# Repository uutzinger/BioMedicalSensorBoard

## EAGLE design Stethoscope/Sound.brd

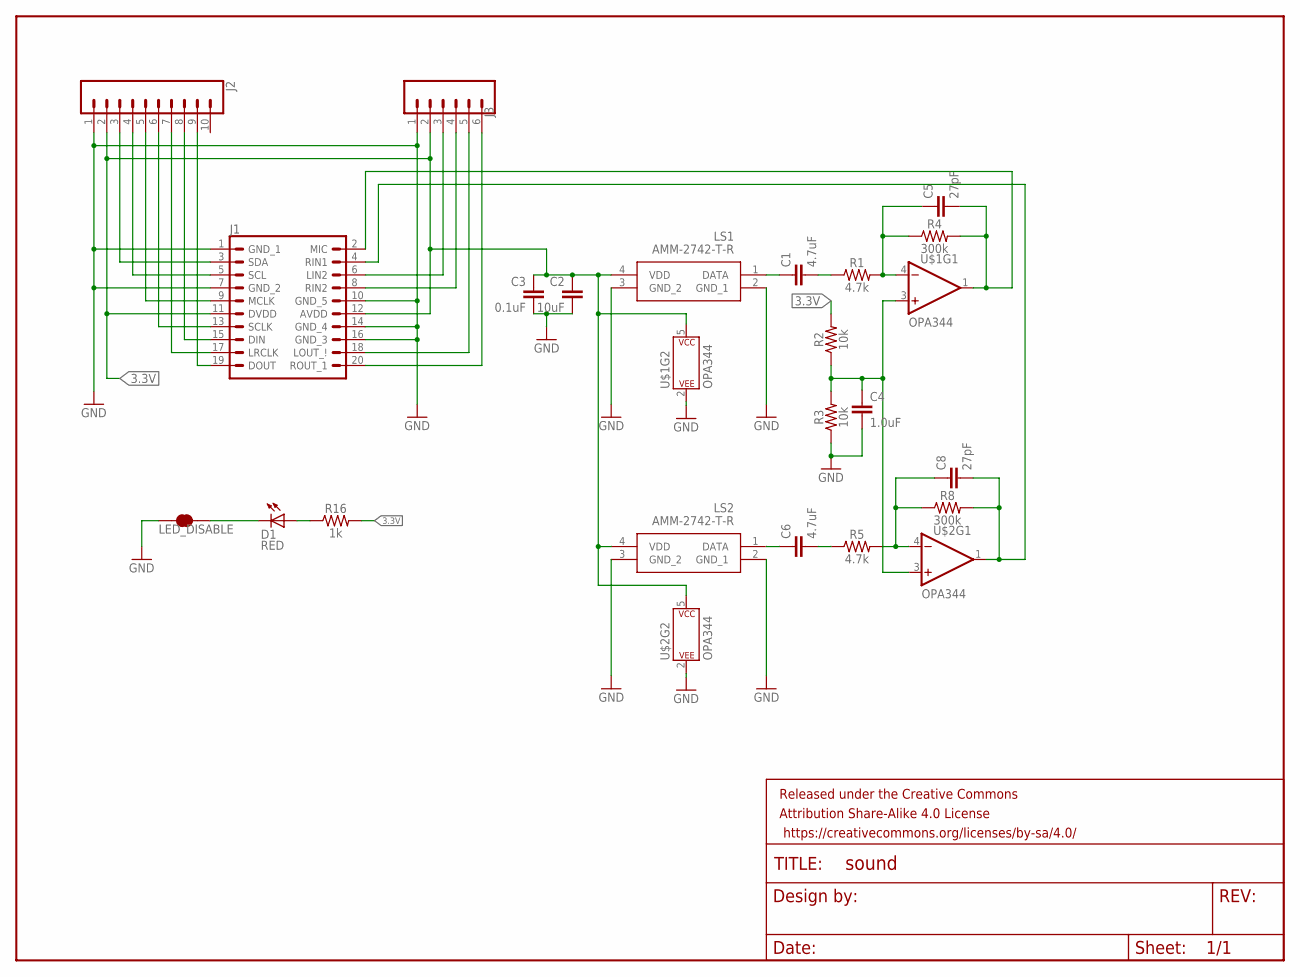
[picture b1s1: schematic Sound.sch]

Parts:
C1, C6: 4.7uF; 0603
C2: 10uF; 0603
C3: 0.1uF; 0603
C4: 1.0uF; 0603
C5, C8: 27pF; 0603
D1: RED; LED-0603
FRAME1: FRAME-LETTERNO_PACKAGE; DUMMY
J1: ES8388ES8388; ES8388
J2: CONN_10"; 1X10
J3: CONN_06SILK_FEMALE_PTH; 1X06
LED_DISABLE: JUMPER-SMT_2_NC_TRACE_SILK; SMT-JUMPER_2_NC_TRACE_SILK
LS1, LS2: AMM-2742-T-R; AMM2742TR
R1, R5: 4.7k; 0603
R2, R3: 10k; 0603
R4, R8: 300k; 0603
R16: 1k; 0603
U$1, U$2: OPA344; SOT23-5

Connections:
3.3V: C2.1, C3.1, J1.11 (DVDD), J1.12 (AVDD), J2.2, J3.2, LS1.4 (VDD), LS2.4 (VDD), R2.2, R16.2, U$1.5 (P$V+), U$2.5 (P$V+)
GND: C2.2, C3.2, C4.2, J1.1 (GND_1), J1.7 (GND_2), J1.10 (GND_5), J1.14 (GND_4), J1.16 (GND_3), J2.1, J3.1, LED_DISABLE.1, LS1.2 (GND_1), LS1.3 (GND_2), LS2.2 (GND_1), LS2.3 (GND_2), R3.1, U$1.2 (P$V-), U$2.2 (P$V-)
unnamed: J1.6 (LIN2), J3.3
unnamed: J1.8 (RIN2), J3.4
unnamed: J1.3 (SDA), J2.3
unnamed: J1.5 (SCL), J2.4
unnamed: J1.9 (MCLK), J2.5
unnamed: J1.13 (SCLK), J2.6
unnamed: J1.15 (DIN), J2.8
unnamed: J1.19 (DOUT), J2.9
unnamed: J1.17 (LRCLK), J2.7
unnamed: J1.18 (LOUT_!), J3.5
unnamed: J1.20 (ROUT_1), J3.6
unnamed: C1.1, LS1.1 (DATA)
unnamed: C5.2, J1.2 (MIC), R4.2, U$1.1 (OUT)
unnamed: C1.2, R1.1
unnamed: C5.1, R1.2, R4.1, U$1.4 (-IN)
unnamed: C4.1, R2.1, R3.2, U$1.3 (+IN), U$2.3 (+IN)
unnamed: C8.2, J1.4 (RIN1), R8.2, U$2.1 (OUT)
unnamed: C6.1, LS2.1 (DATA)
unnamed: C6.2, R5.1
unnamed: C8.1, R5.2, R8.1, U$2.4 (-IN)
unnamed: D1.A, R16.1
unnamed: D1.C, LED_DISABLE.2

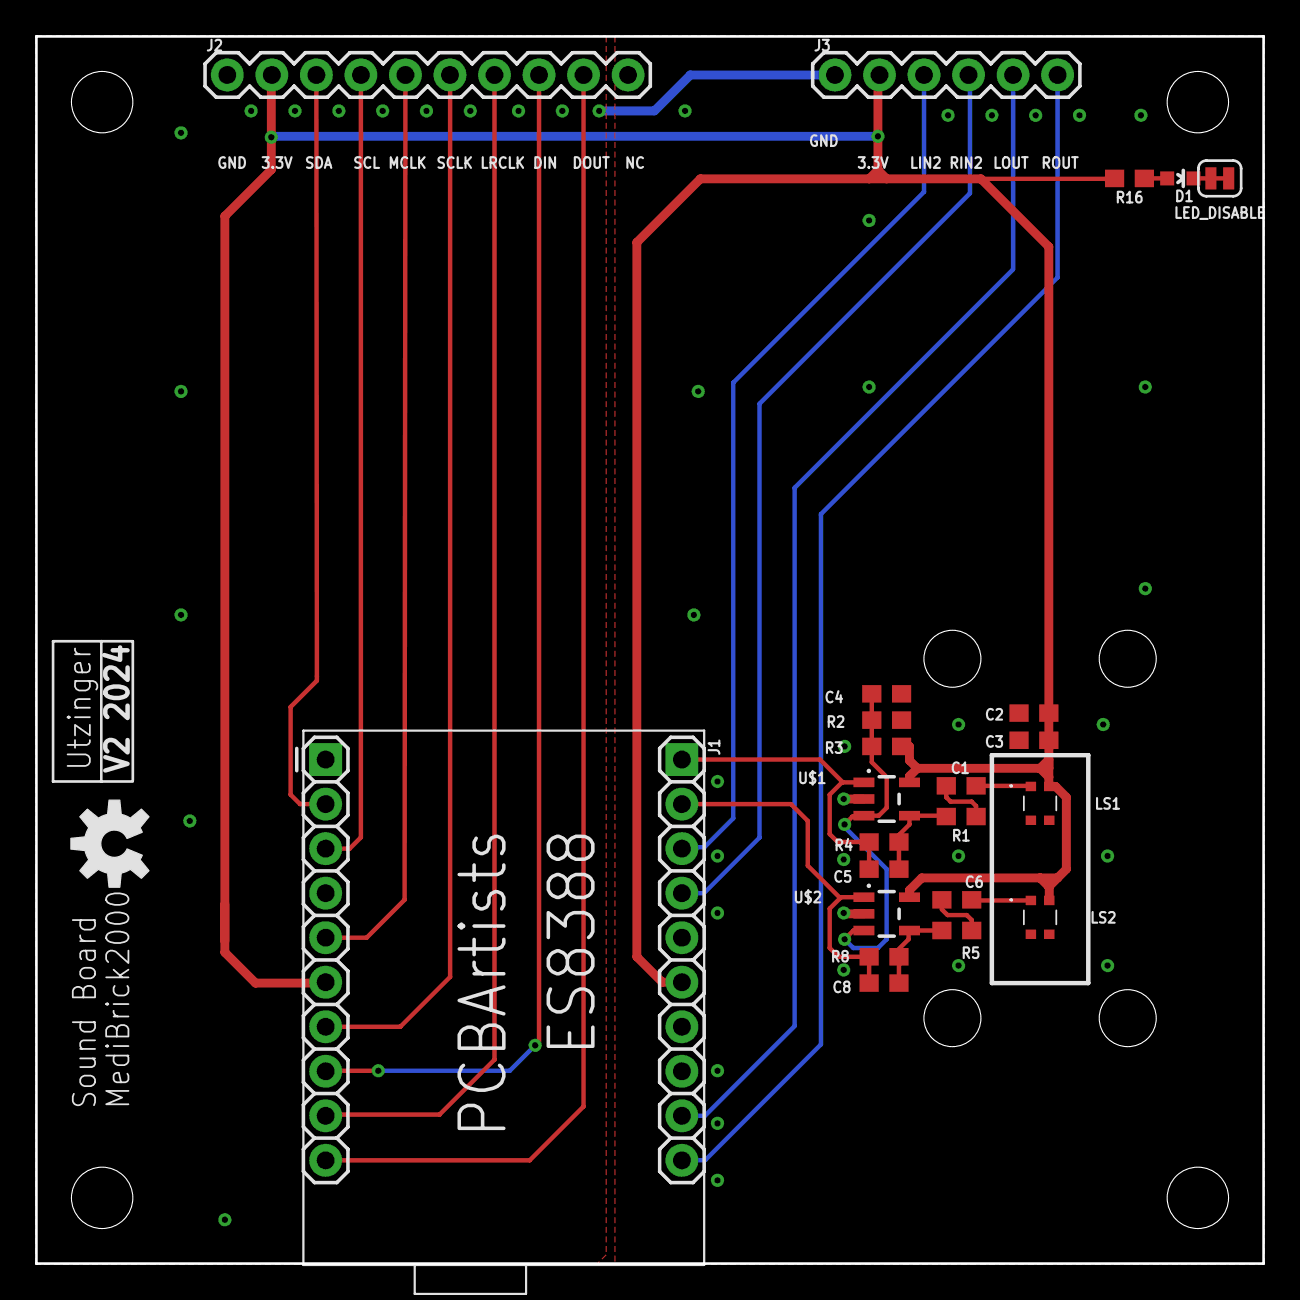
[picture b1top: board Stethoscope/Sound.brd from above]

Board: 2 copper layers, 70.0 x 70.0 mm, 25 parts (0 on the bottom side), 24 nets.

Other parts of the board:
U$3: OSHW-LOGO-M

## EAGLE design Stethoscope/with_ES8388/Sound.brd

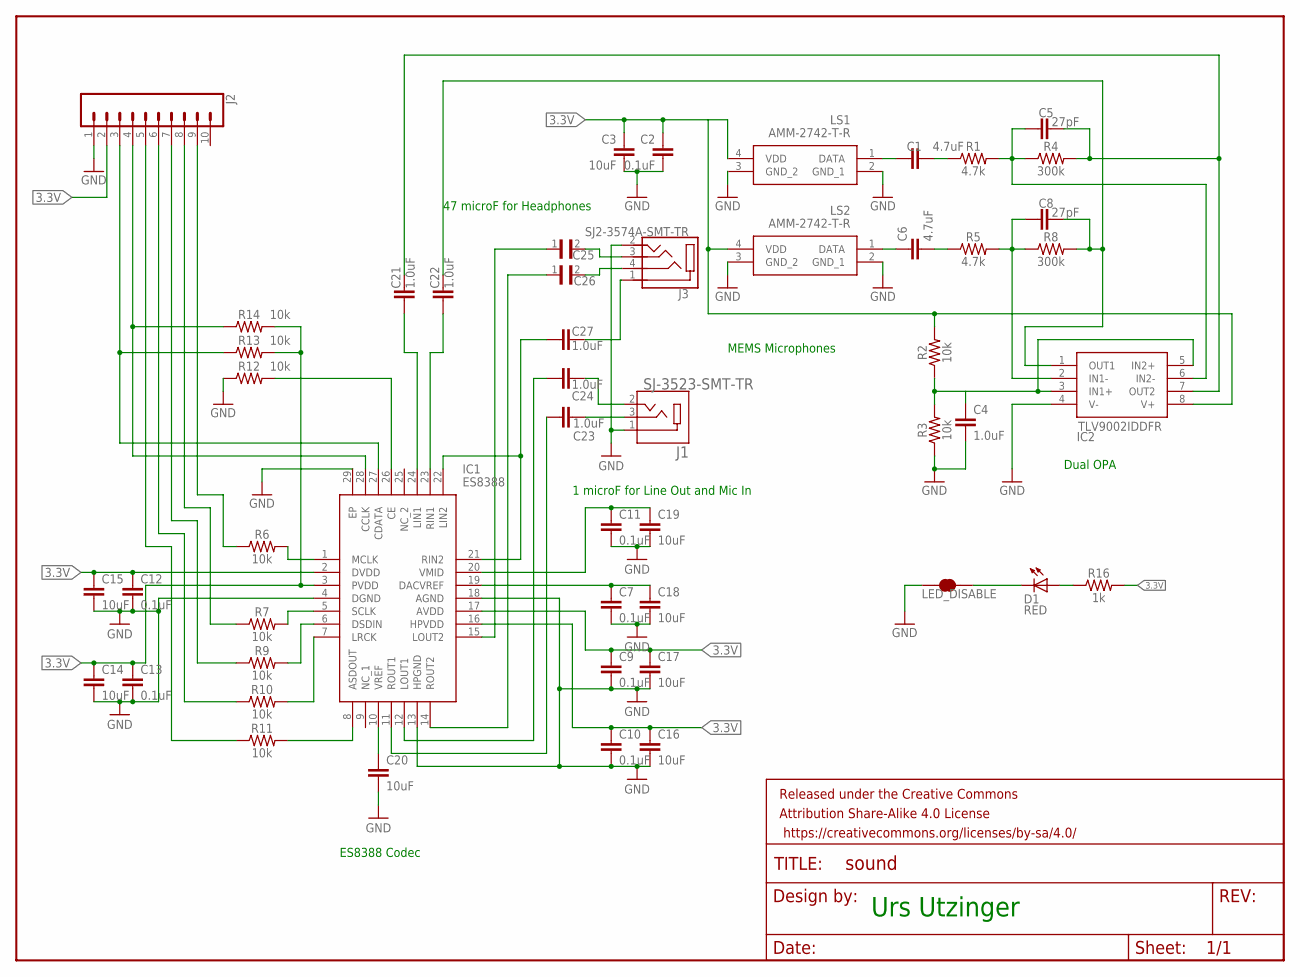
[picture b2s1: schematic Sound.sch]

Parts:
C1, C6: 4.7uF; 0603
C2, C7, C9, C10, C11, C12, C13: 0.1uF; 0603
C3, C14, C15, C16, C17, C18, C19, C20: 10uF; 0603
C4, C21, C22, C23, C24, C27: 1.0uF; 0603
C5, C8: 27pF; 0603
C25, C26: GRM188R60J476ME15D; CAPC1608X100N
D1: RED; LED-0603
FRAME1: FRAME-LETTERNO_PACKAGE; DUMMY
IC1: ES8388; QFN45P400X400X90-29N
IC2: TLV9002IDDFR; SOT65P280X110-8N
J1: SJ-3523-SMT-TR; CUI_SJ-3523-SMT-TR
J2: CONN_10"; 1X10
J3: SJ2-3574A-SMT-TR; CUI_SJ2-3574A-SMT-TR
LED_DISABLE: JUMPER-SMT_2_NC_TRACE_SILK; SMT-JUMPER_2_NC_TRACE_SILK
LS1, LS2: AMM-2742-T-R; AMM2742TR
R1, R5: 4.7k; 0603
R2, R3, R6, R7, R9, R10, R11, R12, R13, R14: 10k; 0603
R4, R8: 300k; 0603
R16: 1k; 0603

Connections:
3.3V: C2.1, C3.1, C9.1, C10.1, C12.1, C13.1, C14.1, C15.1, C16.1, C17.1, IC1.2 (DVDD), IC1.3 (PVDD), IC1.16 (HPVDD), IC1.17 (AVDD), IC2.8 (V+), J2.2, LS1.4 (VDD), LS2.4 (VDD), R2.2, R13.2, R14.2, R16.2
DIN: J2.7, R9.1
DOUT: J2.5, R11.1
GND: C2.2, C3.2, C4.2, C7.2, C9.2, C10.2, C11.2, C12.2, C13.2, C14.2, C15.2, C16.2, C17.2, C18.2, C19.2, C20.2, IC1.4 (DGND), IC1.13 (HPGND), IC1.18 (AGND), IC1.29 (EP), IC2.4 (V-), J1.1, J2.1, J3.2, LED_DISABLE.1, LS1.2 (GND_1), LS1.3 (GND_2), LS2.2 (GND_1), LS2.3 (GND_2), R3.1, R12.1
LRCLK: J2.6, R10.1
MCLK: J2.9, R6.1
unnamed: IC1.26 (CE), R12.2
unnamed: C8.2, C22.2, IC2.1 (OUT1), R8.2
unnamed: C22.1, IC1.23 (RIN1)
unnamed: C21.1, IC1.24 (LIN1)
unnamed: C11.1, C19.1, IC1.20 (VMID)
unnamed: C5.2, C21.2, IC2.7 (OUT2), R4.2
unnamed: C1.1, LS1.1 (DATA)
unnamed: C1.2, R1.1
unnamed: C5.1, IC2.6 (IN2-), R1.2, R4.1
unnamed: C4.1, IC2.3 (IN1+), IC2.5 (IN2+), R2.1, R3.2
unnamed: C6.1, LS2.1 (DATA)
unnamed: C6.2, R5.1
unnamed: C8.1, IC2.2 (IN1-), R5.2, R8.1
unnamed: IC1.8 (ASDOUT), R11.2
unnamed: IC1.7 (LRCK), R10.2
unnamed: C20.1, IC1.10 (VREF)
unnamed: IC1.6 (DSDIN), R9.2
unnamed: IC1.5 (SCLK), R7.2
unnamed: D1.A, R16.1
unnamed: IC1.1 (MCLK), R6.2
unnamed: D1.C, LED_DISABLE.2
unnamed: C23.2, IC1.11 (ROUT1)
unnamed: C24.1, J1.2
unnamed: C7.1, C18.1, IC1.19 (DACVREF)
unnamed: C24.2, IC1.12 (LOUT1)
unnamed: C25.2, J3.3
unnamed: C23.1, J1.3
unnamed: C26.2, J3.4
unnamed: C27.2, J3.1
unnamed: C27.1, IC1.21 (RIN2), IC1.22 (LIN2)
unnamed: C26.1, IC1.14 (ROUT2)
unnamed: C25.1, IC1.15 (LOUT2)
SCL: IC1.28 (CCLK), J2.4, R14.1
SCLK: J2.8, R7.1
SDA: IC1.27 (CDATA), J2.3, R13.1

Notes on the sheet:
MEMS Microphones
Dual OPA
47 microF for Headphones
1 microF for Line Out and Mic In
Urs Utzinger
ES8388 Codec

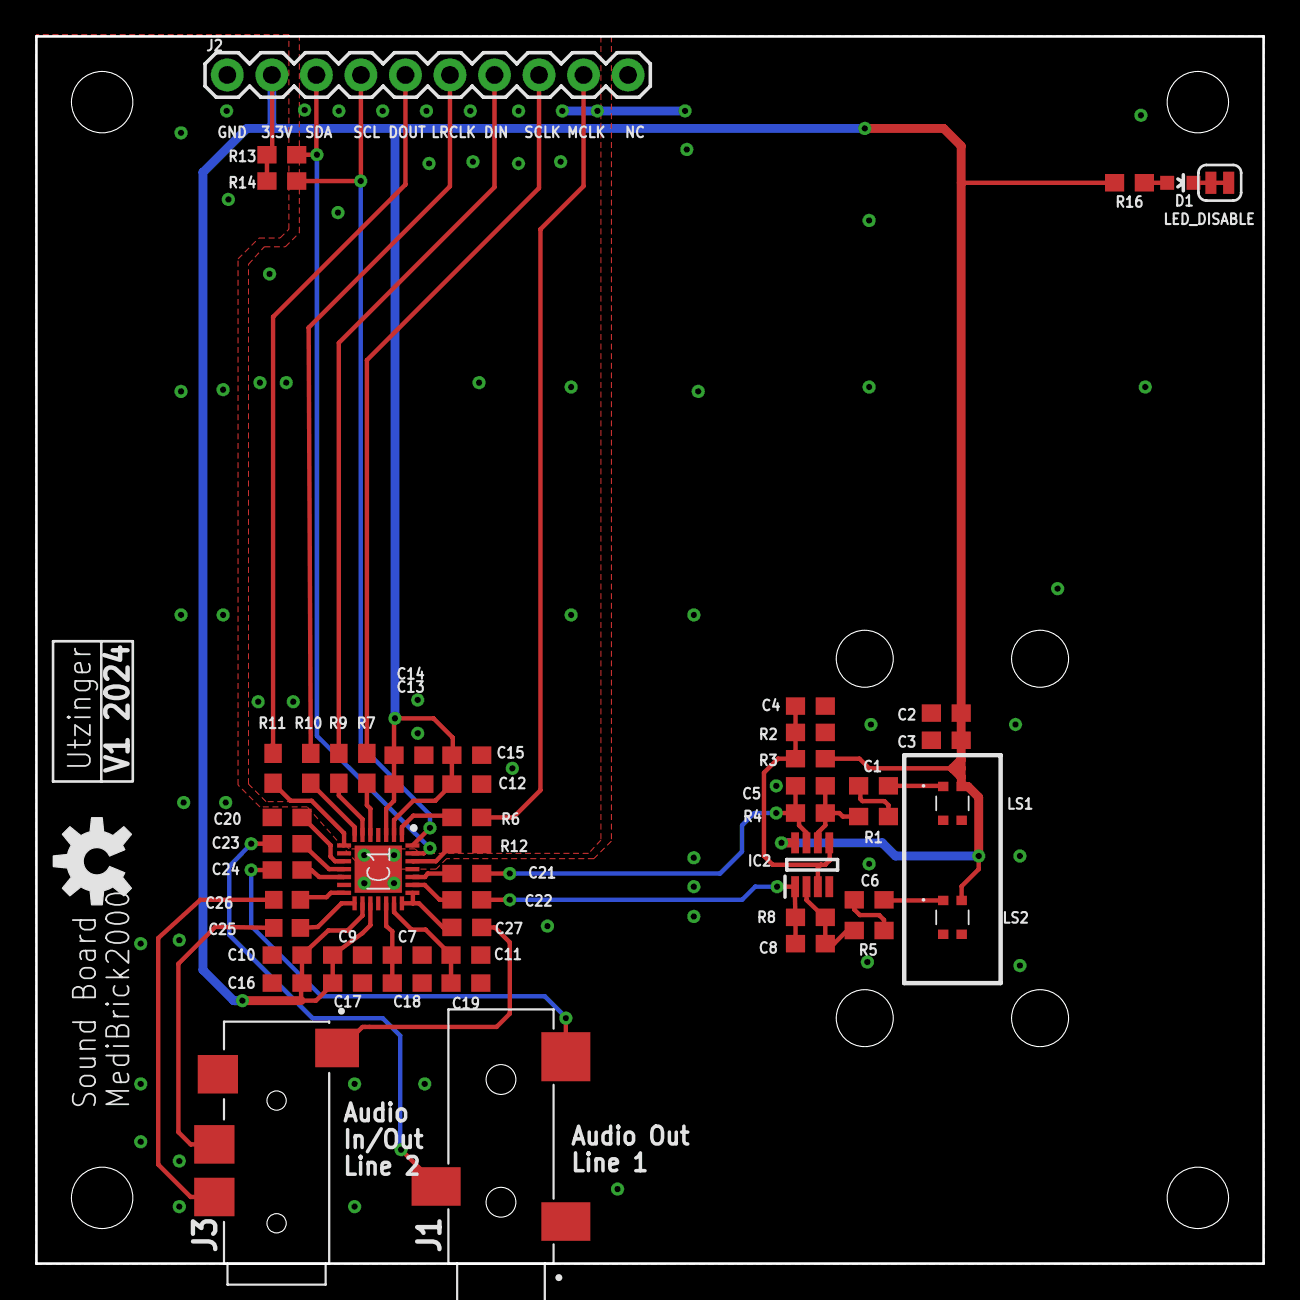
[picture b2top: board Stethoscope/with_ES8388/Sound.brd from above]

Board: 2 copper layers, 70.0 x 70.0 mm, 53 parts (0 on the bottom side), 41 nets.

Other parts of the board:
U$3: OSHW-LOGO-M

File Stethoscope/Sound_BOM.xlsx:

Item # | Designator | Qty | Manufacturer | Mfg Part # | LCSC Part# | U.S. Distributor | Description / Value | *Package/Footprint | Mounting Type | Your Instructions / Notes
1 | C2, C7, C9, C10, C11, C12, C13, C28 | 8 | Samsung Electro-Mechanics | CL10B104KA8NNNC | C1590 |  | 0.1uF | 0603 | SMD
2 | C4, C21, C22, C23, C24, C27 | 6 | Samsung Electro-Mechanics | CL10A105KA8NNNC | C5673 |  | 1.0uF | 0603 | SMD
3 | C3, C14, C15, C16, C17, C18, C19, C20, C29 | 9 | Samsung Electro-Mechanics | CL10A106MA8NRNC | C96446 |  | 10uF | 0603 | SMD
4 | C1, C6 | 2 | Samsung Electro-Mechanics | CL10A475KA8NQNC | C69335 |  | 4.7uF | 0603 | SMD
5 | C5, C8 | 2 | Samsung Electro-Mechanics | CL10C270JB81PNC | C346211 |  | 27pF | 0603 | SMD
6 | C25, C26 | 2 | Samsung Electro-Mechanics | CL10A476MQ8QRNC | C730416 |  | 47uF | 0603 | SMD
7 | C30 | 1 | Samsung Electro-Mechanics | CL10B102KB8NNNC | C1588 |  | 1nF | 0603 | SMD
8 | R1, R5 | 2 | YAGEO | RC0603FR-074K7L | C99782 |  | 4.7k | 0603 | SMD
9 | R2, R3, R12, R13, R14 | 5 | YAGEO | RC0603FR-0710KL | C98220 |  | 10k | 0603 | SMD
10 | R4, R8 | 2 | YAGEO | RC0603FR-07300KL | C114667 |  | 300k | 0603 | SMD
11 | R6, R7, R9, R10, R11, R15, R17 | 7 | YAGEO | RC0603FR-0733RL | C108661 |  | 33 | 0603 | SMD
12 | R16 | 1 | YAGEO | RC0603FR-071KL | C22548 |  | 1k | 0603 | SMD
13 | LS1, LS2 | 2 | PUI Audio, Inc. | AMM-2742-T-R | C3171735 | https://www.mouser.com/ProductDetail/PUI-Audio/AMM-2742-T-R?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 | AMM-2742-T-R, MEMS Microphones | 0603 | SMD |  | 1.5
14 | IC1 | 1 | Everest-semi(Everest Semiconductor) | ES8388 | C365736 |  | ES8388 | QFN-28-EP(4x4) | SMD |  | 1
15 | U1 | 1 | Honeywell | MPRLS0300YG00001BB |  | https://www.mouser.com/ProductDetail/Honeywell/MPRLS0300YG00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 | MPRLS0300YG00001B |  | SMD |  | 13.42
16 | D1 | 1 | XINGLIGHT | XL-1608UBC-04 | C965807 |  | Blue LED | 0603 | SMD
17 | J1 | 1 | CUI Devices | SJ-3523-SMT-TR |  | https://www.mouser.com/ProductDetail/CUI-Devices/SJ-3523-SMT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 | SJ-3523-SMT-TR, 3.5mm Audio Jack |  | SMD |  | 0.93
18 | J3 | 1 | CUI Devices | SJ2-3574A-SMT-TR |  | https://www.mouser.com/ProductDetail/CUI-Devices/SJ2-3574A-S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 | SJ2-3574A-SMT-TR, 3.5mm Audio Jack with microphone |  | SMD |  | 1.12
19 | IC2 | 1 | Texas Instruments | TLV9002IDDFR | C2862620 |  | TLV9002IDDFR, Dual OpAmp | TSOT-23-8 | SMD |  | 0.2
 |  | 55

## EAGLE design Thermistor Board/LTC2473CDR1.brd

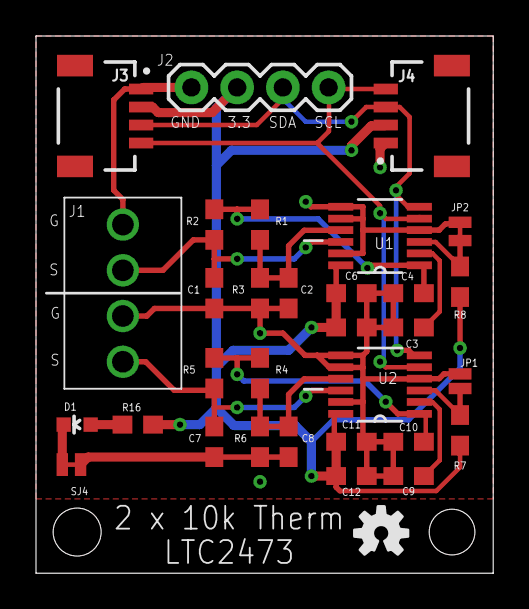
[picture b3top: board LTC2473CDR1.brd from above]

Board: 2 copper layers, 25.4 x 29.8 mm, 33 parts (0 on the bottom side), 16 nets.

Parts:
C1, C2, C3, C4, C5, C7, C8, C9, C10, C11: 0.1uF; 0603
C6, C12: 10uF; 0603
D1: RED; LED-0603
FRAME1: FRAME-LETTERNO_PACKAGE; DUMMY
J1: 282834-4; 2828344
J2: I2C; 1X04
J3, J4: I2C; JST04_1MM_RA
JP1: JUMPER-SMT_2_NO_NO-SILK; SMT-JUMPER_2_NO_NO-SILK
JP2: JUMPER-SMT_2_NC_TRACE_NO-SILK; SMT-JUMPER_2_NC_TRACE_NO-SILK
R1, R2, R3, R4, R5, R6, R7, R8: 10k; 0603
R16: 1k; 0603
SJ4: LED DISABLE; SMT-JUMPER_2_NC_TRACE_NO-SILK
U1, U2: LTC2473IMS#PBF; SOP65P490X110-12N
U$1: OSHW-LOGO-S

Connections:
3.3V: C5.1, C6.1, C11.1, C12.1, J2.2, J3.2, J4.2, R7.2, R8.2, R16.2, U1.12, U2.12
GND: C1.2, C2.2, C3.2, C4.2, C5.2, C6.2, C7.2, C8.2, C9.2, C10.2, C11.2, C12.2, J1.2, J1.4, J2.1, J3.1, J4.1, JP1.1, JP2.1, R3.1, R6.1, SJ4.1, U1.4, U1.7, U1.8, U1.11, U2.4, U2.7, U2.8, U2.11
unnamed: C3.1, U1.2
unnamed: C2.1, R1.1, R3.2, U1.9
unnamed: C8.1, R4.1, R6.2, U2.9
unnamed: C4.1, R1.2, R2.2, U1.1
unnamed: JP1.2, R7.1, U2.3
unnamed: D1.A, R16.1
unnamed: C7.1, J1.1, R5.1, U2.10
unnamed: C10.1, R4.2, R5.2, U2.1
unnamed: D1.C, SJ4.2
unnamed: C9.1, U2.2
unnamed: C1.1, J1.3, R2.1, U1.10
unnamed: JP2.2, R8.1, U1.3
SCL: J2.4, J3.4, J4.4, U1.5, U2.5
SDA: J2.3, J3.3, J4.3, U1.6, U2.6

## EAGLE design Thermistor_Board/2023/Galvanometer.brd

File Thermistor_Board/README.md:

# Thermistor/Wheatstone Brick

This Thermistor solution is based on a calibrated Wheatstone bridge. The Voltage potential over the thermistor is measured  and compared to a fixed voltage divider. Three thermistors can be measured using the micro controllers internal analog to digital converter. In order to achieve accuracy, the ADC is run a audio frequencies and measurements are averaged. Although ESP32 internal ADC is not of high quality, with the help of linearization and signal averaging, accurate temperature readings are achieved. 

## Costs &#36;

| Item        | Quantity at Purchase | Costs  | Source            | Cost per Brick
|---                          | ---  | ---    | ---               | ---
| Microcontroller             |  1   | $17.5  | [Adafruit](https://www.adafruit.com/product/5477)          | $17.5
| Display                     |  5   | $13    | [Amazon](https://a.co/d/1QH0Ab9)            | $3
| Button                      | 25   | $9     | [Amazon](https://a.co/d/8KAuTwC) | $0.5 
| Battery                     |  1   | $10     | [Adafruit](https://www.adafruit.com/product/258)        | $10
| PCB                         |  5   | $45.20  | PCBWay            | $9
| Parts and Assembly          |  2   | $99.16* | PCBWay            | $50
| Thermistors MA1000GG103AN **|  1   | $6      | [Amphenol](https://www.mouser.com/ProductDetail/Amphenol-Advanced-Sensors/MA100BF103AN?qs=wrT8kFYR7791l5TjYdzP%252BA%3D%3D) | $6
| 3.5mm male audio connector  | 10   | $10    | [Amazon](https://a.co/d/bbEIi9s) | $1
| Assorted Wires              |8m    | $15    | [Amazon](https://a.co/d/58djefc) | $1
| Assorted Screws and Nuts    |100   |  $7    | Amazon            | $0.05
| Assorted 3D printed parts   |      |        |  | $3
|                             |      |        |                   |
| **Total**                   |      |        |                   | **$100**

*Electronic components are $12 per board. 

**MA100BF103 also comes in less accurate and less expensive versions: MA100BF103BN and  MA100BF103CN.

## Test Software &#128187;
Test software is located in the Arduino folder.

| Folder | Description | 
|--- |---|
|MediBrick_Temperature_Test | Computes calibrated temperature. |

## Microcontroller Software : &#9000;
Not finalized yet

## Electronics Design &#128268;

The following files are needed for PCB manufacturing and assembly.

- [Bill of Materials](Temp_BOM.xlsx)
- [Manufacturing Files](Temp_2024-07-16.zip)
- [Pick and Place](Temp_PnP.xlsx)

The Bill of Materials is formatted so that its compatible with PCBWay submissions.

## 3D Printed Parts &#9881;
These are the links to the OnShape Design files, which you can edit and modify if you have an OnShape account (OnShape has free academic accounts).

- Medi Brick
  - [Brick Top](https://cad.onshape.com/documents/be6b7e5f847d89f3ec5eb9d5/w/761fee9865ca7ef709028476/e/ff897b4f359cec83b782ff14)
  - [Brick Bottom](https://cad.onshape.com/documents/92ad78475e8f0b17ff5e260b/w/88a02abbcb12cdbd4d9de3ad/e/fb79ca58ad2b6a0298e9d1b6)
  - [Brick Assembly](https://cad.onshape.com/documents/11cbfe9c3c739b6e8ecbf3d7/w/989b564ecd7f6d069e643ac0/e/85542f706be8cc7554218e8d)
  - [Temperature Brick Side Plate](https://cad.onshape.com/documents/dac7e67c5b0270015712d245/w/d60526c34fb0e9aab2c02a4b/e/a363f2f519f137cd253c6eda?renderMode=0&uiState=6712d9ca15dc976491f436f6)

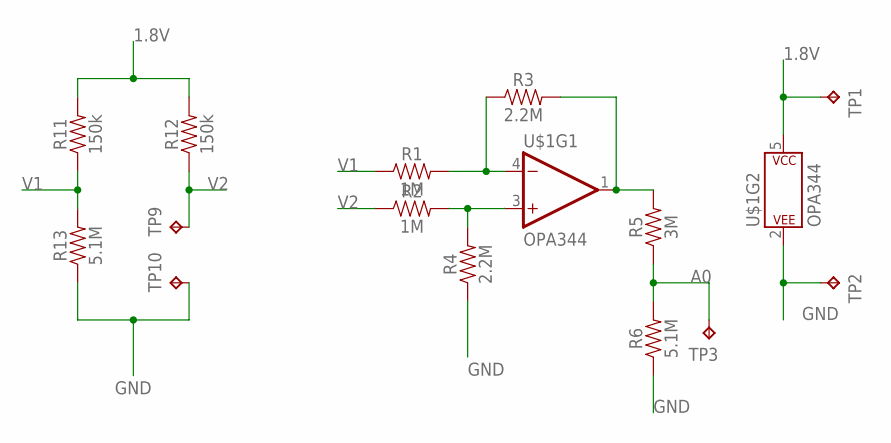
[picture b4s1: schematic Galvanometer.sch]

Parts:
R1, R2: 1M; 0603
R3, R4: 2.2M; 0603
R5: 3M; 0603
R6, R13: 5.1M; 0603
R11, R12: 150k; 0603
TP1, TP2, TP3, TP9, TP10: TPTP19R; TP19R
U$1: OPA344; SOT23-5

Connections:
1.8V: R11.2, R12.2, TP1.TP, U$1.5 (P$V+)
A0: R5.1, R6.2, TP3.TP
GND: R4.1, R6.1, R13.1, TP2.TP, TP10.TP, U$1.2 (P$V-)
unnamed: R1.2, R3.1, U$1.4 (-IN)
unnamed: R2.2, R4.2, U$1.3 (+IN)
unnamed: R3.2, R5.2, U$1.1 (OUT)
V1: R1.1, R11.1, R13.2
V2: R2.1, R12.1, TP9.TP

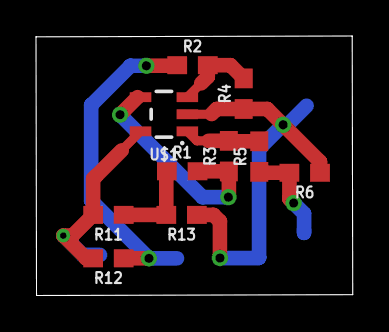
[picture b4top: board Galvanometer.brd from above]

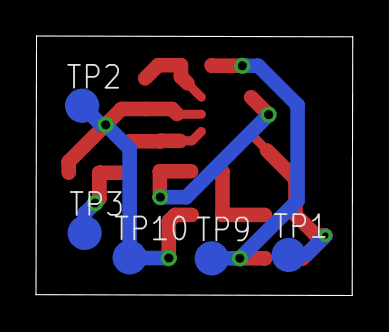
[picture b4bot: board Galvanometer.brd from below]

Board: 2 copper layers, 17.6 x 14.4 mm, 15 parts (5 on the bottom side), 8 nets.

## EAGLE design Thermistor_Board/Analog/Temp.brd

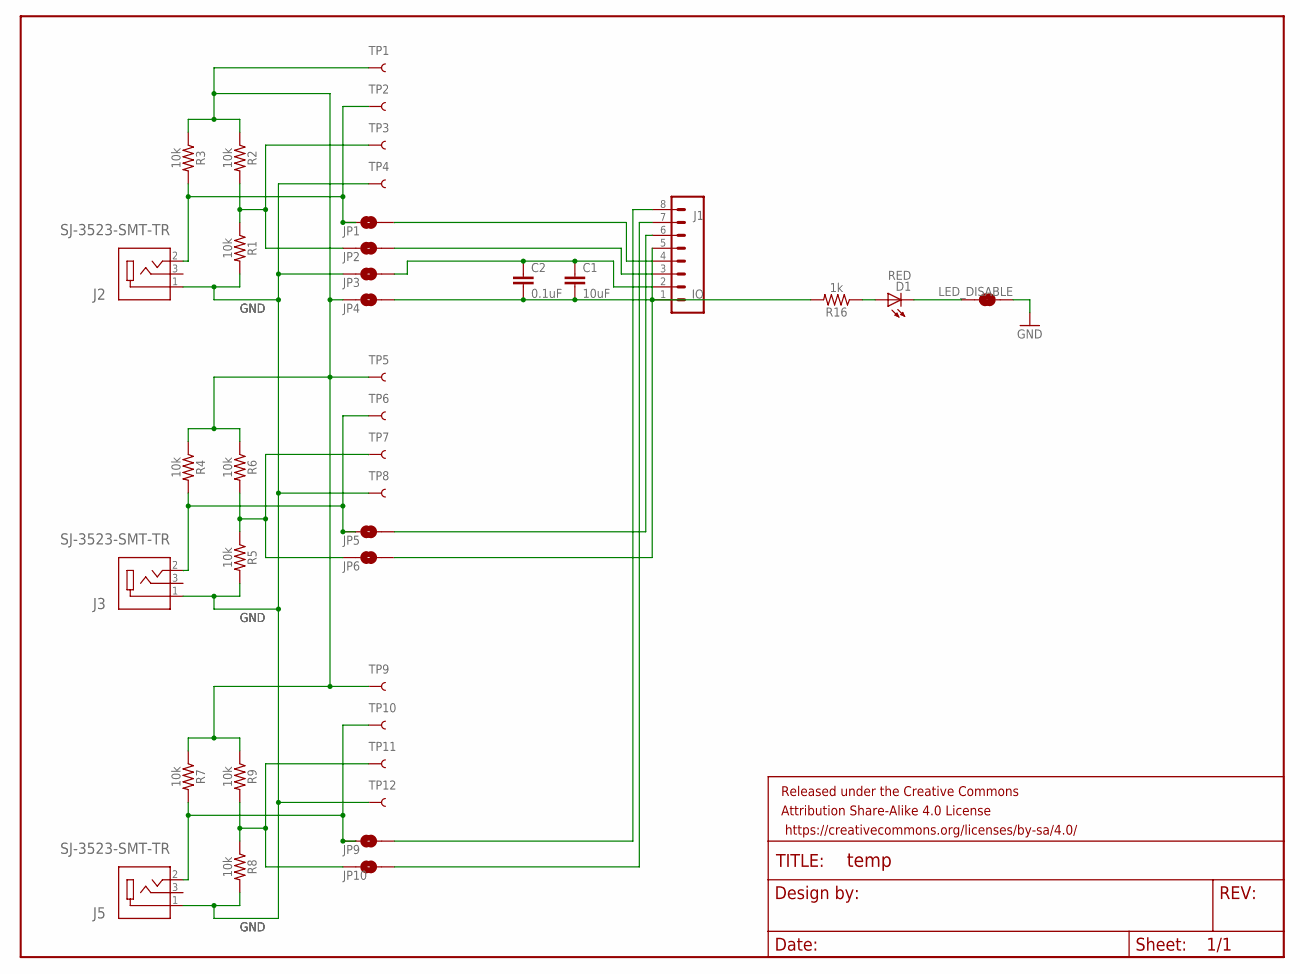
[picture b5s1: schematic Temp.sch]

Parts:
C1: 10uF; 0603
C2: 0.1uF; 0603
D1: RED; LED-0603
FRAME1: FRAME-LETTERNO_PACKAGE; DUMMY
J1: IO; 1X08
J2, J3, J5: SJ-3523-SMT-TR; CUI_SJ-3523-SMT-TR
JP1, JP2, JP3, JP4, JP5, JP6, JP9, JP10: JUMPER-SMT_2_NO_NO-SILK; SMT-JUMPER_2_NO_NO-SILK
LED_DISABLE: JUMPER-SMT_2_NC_TRACE_SILK; SMT-JUMPER_2_NC_TRACE_SILK
R1, R2, R3, R4, R5, R6, R7, R8, R9: 10k; 0603
R16: 1k; 0603
TP1, TP2, TP3, TP4, TP5, TP6, TP7, TP8, TP9, TP10, TP11, TP12: TEST-POINT3X5; PAD.03X.05

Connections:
3.3V: JP4.1, R2.1, R3.1, R4.1, R6.1, R7.1, R9.1, TP1.P$1, TP5.P$1, TP9.P$1
GND: J2.1, J3.1, J5.1, JP3.1, LED_DISABLE.1, R1.2, R5.2, R8.2, TP4.P$1, TP8.P$1, TP12.P$1
unnamed: JP6.1, R5.1, R6.2, TP7.P$1
unnamed: JP2.1, R1.1, R2.2, TP3.P$1
unnamed: J1.3, JP2.2
unnamed: J2.2, JP1.1, R3.2, TP2.P$1
unnamed: J1.4, JP1.2
unnamed: J3.2, JP5.1, R4.2, TP6.P$1
unnamed: J1.7, JP10.2
unnamed: J1.8, JP9.2
unnamed: J1.6, JP5.2
unnamed: JP10.1, R8.1, R9.2, TP11.P$1
unnamed: J5.2, JP9.1, R7.2, TP10.P$1
unnamed: C1.2, C2.2, J1.1, JP4.2, R16.2
unnamed: C1.1, C2.1, J1.2, J1.5, JP3.2, JP6.2
unnamed: D1.A, R16.1
unnamed: D1.C, LED_DISABLE.2

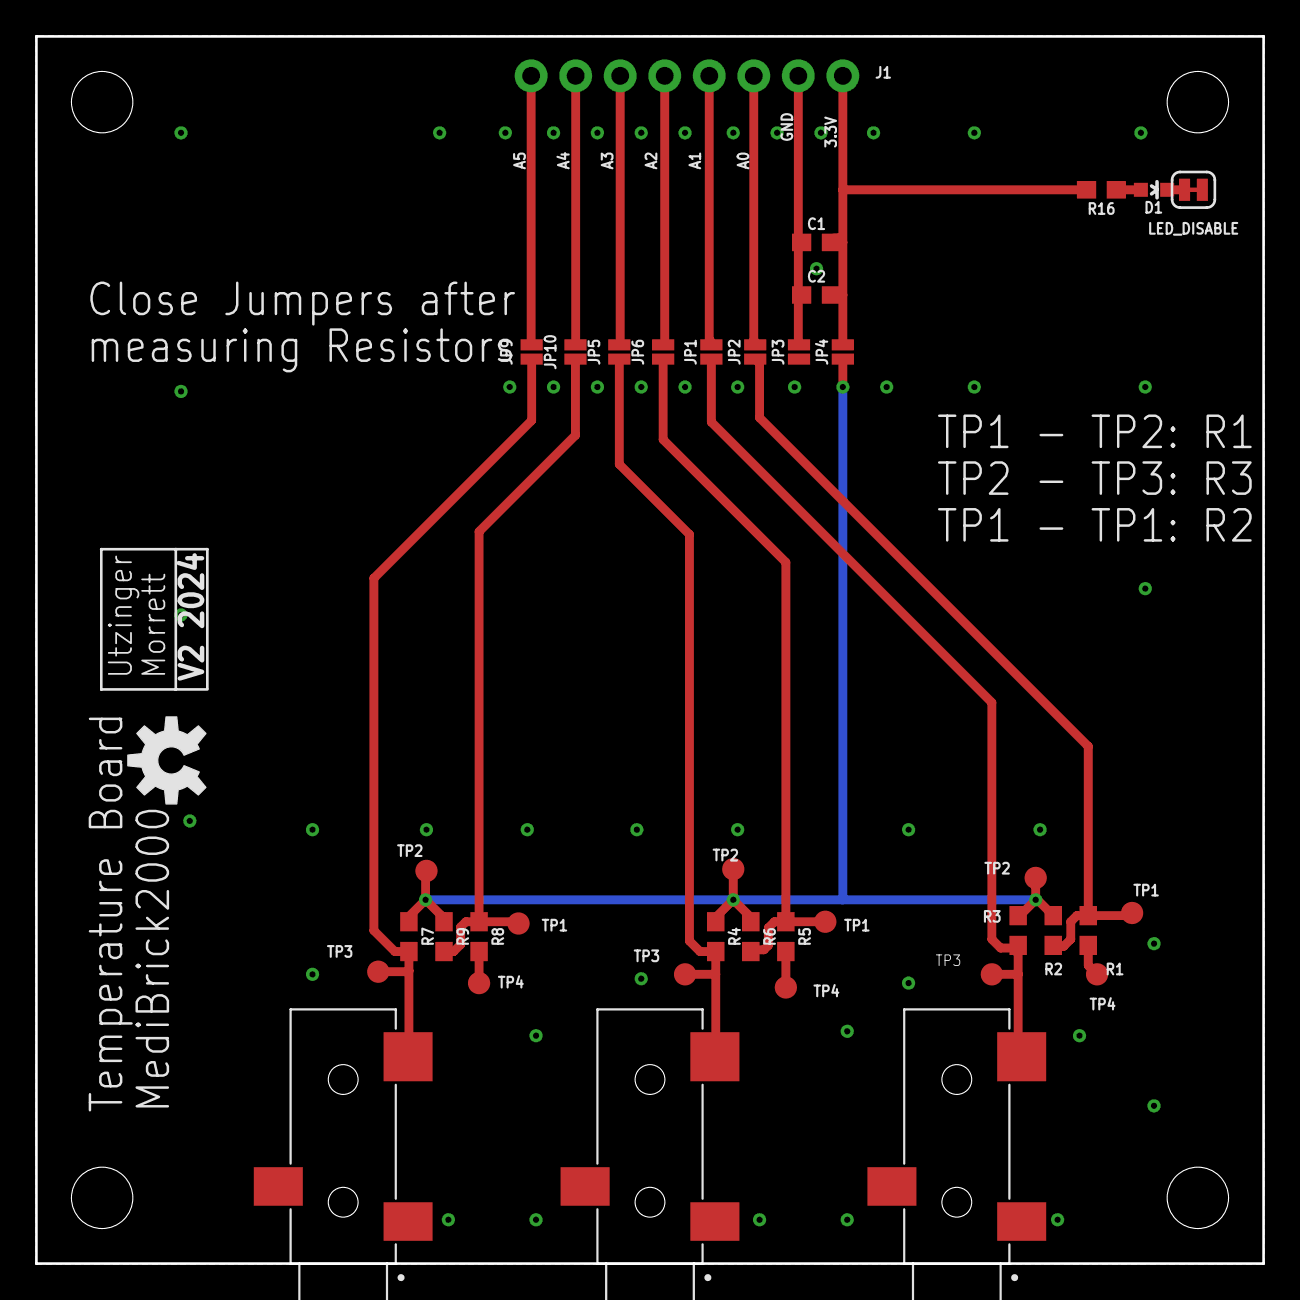
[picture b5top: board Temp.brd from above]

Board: 2 copper layers, 70.0 x 70.0 mm, 40 parts (1 on the bottom side), 17 nets.

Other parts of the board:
U$1: OSHW-LOGO-M

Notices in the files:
parts and their libraries:
SparkFun-Jumpers: Licensing: Creative Commons ShareAlike 4.0 International - https://creativecommons.org/licenses/by-sa/4.0
SparkFun-LED: Licensing: CC v3.0 Share-Alike You are welcome to use this library for commercial purposes.
SparkFun-Aesthetics: https://creativecommons.org/licenses/by-sa/4.0
